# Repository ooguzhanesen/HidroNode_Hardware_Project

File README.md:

# STM32WL HidroNode – Donanım Tasarım Dokümantasyonu

> **Hazırlayan:** Oğuzhan ESEN  
> **Proje Adı:** HidroNode Board 
> **Tarih:** 24 Eylül 2025  
> **Versiyon:** v1.0
---

## İçindekiler

1. [Giriş](#1-giriş)  
2. [Tasarımın Amacı ve Kapsamı](#2-tasarımın-amacı-ve-kapsamı)  
3. [Sistem Blok Diyagramı](#3-sistem-blok-diyagramı)  
4. [Tasarım Özeti](#4-tasarım-özeti)  
5. [Şematik ve PCB](#5-şematik-ve-pcb)  
6. [Test Notları](#6-test-notları)  
7. [Geliştirme ve İyileştirme Önerileri](#7-geliştirme-ve-iyileştirme-önerileri)
---

## 1. Giriş

Bu doküman, LoraSOM Kartının taşıyıcısını  olan HidroNode kartını açıklamayı amaçlamaktadır. 
Tasarım, aşağıdaki isterleri karşılamak üzere gerçekleştirilmiştir:

- LoraSOM kartı ile pin uyumu sağlanması.
- Sensörlerle Dijital haberleşme yapabilmesi için **(TPEC)** RS485 engtegresinin bulunması.
- Sensörlerle Analog haberleşme yapabilmesi için **(Radar)** 4-20mA okuma girişinin bulunması.
- Dijital çıkış ile çalışan sensörlerden veri okuyabilmesi için **(Yağmur Sensörü)** dijital girişin bulunması.
- Arazi koşullarında Akü ve benzeri bataryalarla çalışabilmesi için 7-28 V girişi regüle edebilesi.
- Sensör çıkışlarının votajının sabitlenmesi(15v).
- Tassaruf amacıyla sensorleri kullanılmadığında kapatması.
- Dijital giriş çıkışların izole edilmesi.

---

## 2. Tasarımın Amacı ve Kapsamı
Proje kapsamında, LoraSOM kartının güvenli şekilde sensörlerden gelen verileri okuması ve çevresel şartlarda çalışması amaçlanmaktadır.

Taşıyıcı kart, aşağıdaki teknik özellikleri ile ölçüm istasyonlarındaki ihtiyaçları karşılamaktadır:

- **RS485 Haberleşme**  
  MAX3075EESA entegresi ile TPEC gibi endüstriyel sensörler ile haberleşme sağlanır.

- **Analog Sensör Girişi (4–20 mA)**  
  150 Ω shunt direnç, 2 adet opamp ve zener koruma ile akım döngülü sensörlerden gelen analog değer 16 bit çözünürlüğe sahip ADS1115IDGS entegresine bağlanır. Bu entegre de I2C ile LoraSOM'a Bağlıdır.

- **Panel Gerilim Okuma**  
  150 kΩ ve 20 kΩ direnç bölücü ile güneş panelinden voltaj ölçümü yapılabilir.

- **İzole Dijital Giriş**  
  Optokuplör korumalı 2 adet dijital giriş ile dijital çıkışlı ( yağmur sensörü) sensörlerden veri okunabilir.

- **İzole Dijital Çıkışlar**  
  4 adet dijital çıkış LTV-847S entegresi sayesinde izole şekilde röle veya kontrol elemanları sürülebilir.

- **Geniş Giriş Gerilim Aralığı**  
  TPS54302 ve TPS62291DRVR entegreleri ile 7–28 V DC giriş, 5 V ve 3.3 V seviyelerine güvenli şekilde regüle edilir.

- **Sensör Güç çıkışlarının Sabitlenmesi ve Kontrolü (15V)**  
  MT3608 entegresi ile 5v 15v yükselterek sensörlerin akü voltajına bağımlı kalması engellenmiştir. Ayrıca MT3608 entegresin enable pini ile bu çıkışlar anahtarlanmaktadır. 

---

## 3. Sistem Blok Diyagramı

## 4. Tasarım Özeti

Tasarım 4 katlı olacak şekikde KiCAD üzerinden tasarlanmıştır.

## 5. Şematik ve PCB
[Şematik için tıklayın](docs/HidroNode_Project.pdf)

.jpeg)

---
## 6. Test Notları
* 5v regülatör devresinde 75pf olmadıgı için en yakın deger olan 68pf kullanıldı.

---
## 7. Geliştirme ve İyileştirme Önerileri

* indüktör footprinti güncellenebilir.
* tvs diyot kıfı küçültülebilir.
* Genişleme portunun slikscreeni düzeltilecek. 
* Kart soket tipi degistirilebilir 

--- 

## Eksikler
* Anten kablosu alınacak.
* kart montajı için vida alınacak
* genişleme portu karsılık soketi alınacak
* hoparlor modulunun voltajı 3.3 volta dusurulecek.
* sbrr alınması gerek. 1 adet kaldı.  
* 150 ohm sont bitti.

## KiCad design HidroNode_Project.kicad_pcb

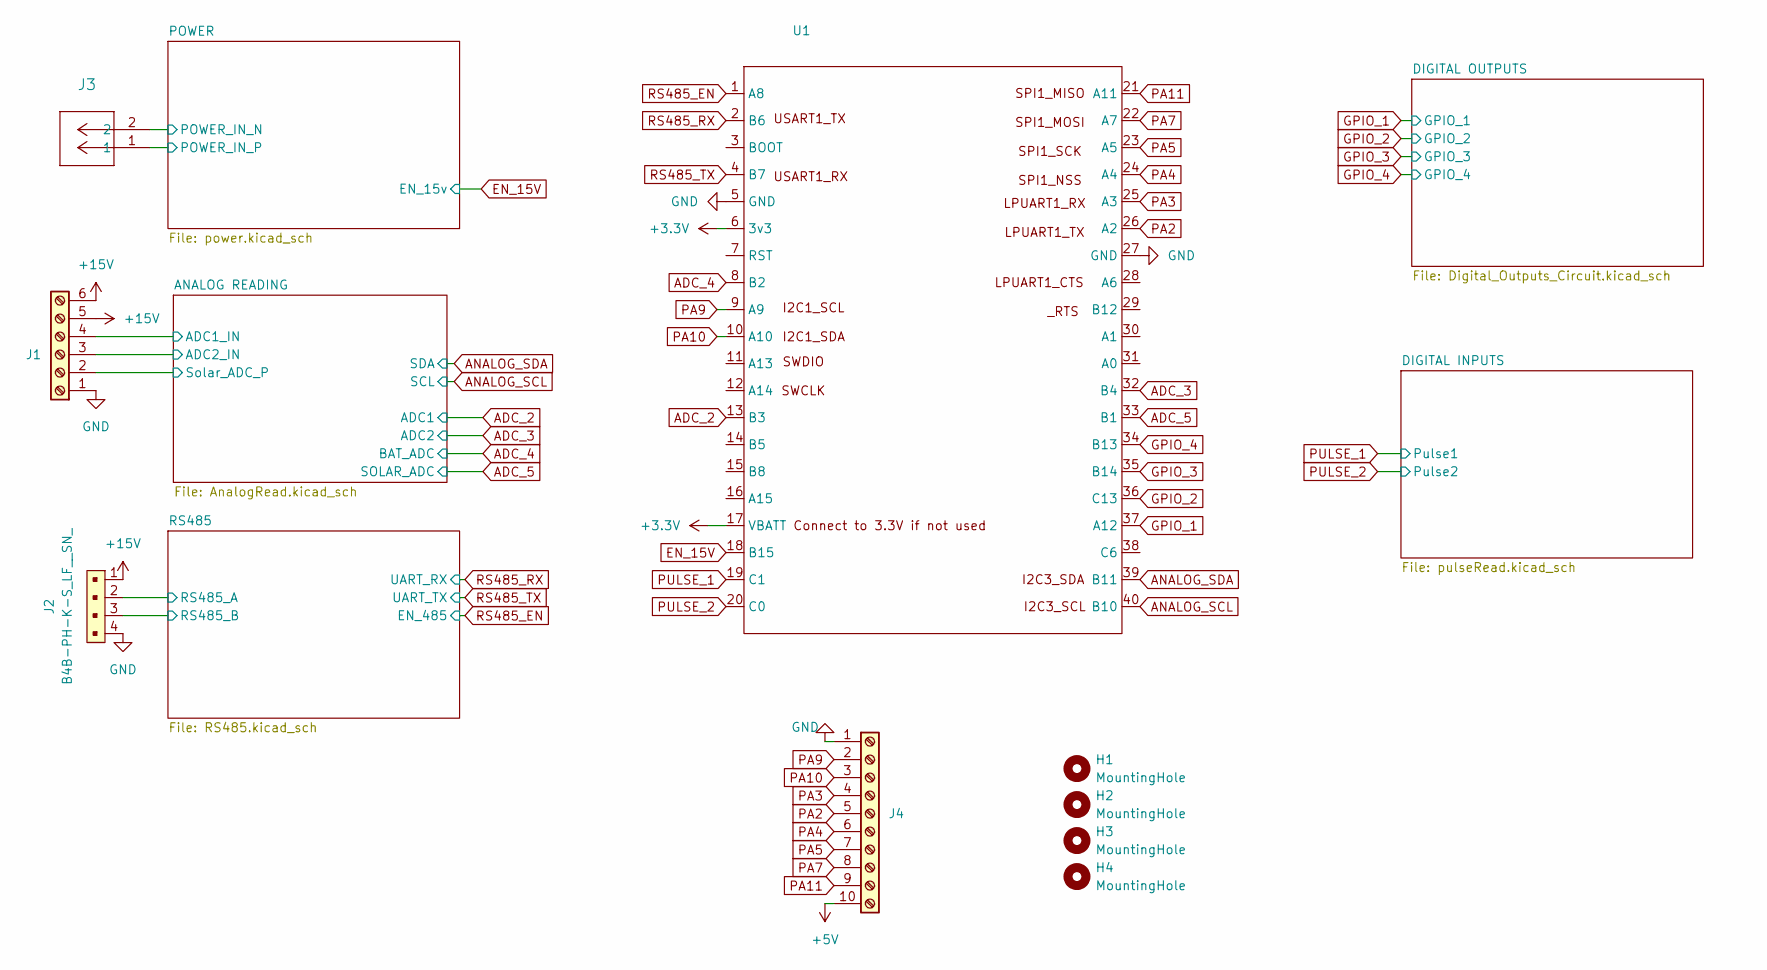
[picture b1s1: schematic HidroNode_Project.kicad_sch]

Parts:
H1, H2: MountingHole; MountingHole_3.2mm_M3_ISO14580_Pad
H3, H4: MountingHole; MountingHole_2.7mm_M2.5_DIN965_Pad
J1: Hirose_DF13-06P-1.25DSA_1x06_P1.25mm_Vertical
J2: B4B-PH-K-S_LF__SN_; Hirose_DF13-04P-1.25DSA_1x04_P1.25mm_Vertical; MPN B4B-PH-K-S(LF)(SN); Digi-Key_PN 455-1706-ND
J3: PinHeader_2x01_P2.54mm_Vertical
J4: BoxHeader2x5_1.27
U1: stm32wl_lora_som

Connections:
+3.3V: U1.6 (3v3), U1.17 (VBATT); also elsewhere on the board
+5V: J4.10; also elsewhere on the board
+15V: J1.5, J1.6, J2.1; also elsewhere on the board
/ANALOG READING/ADC1_IN: J1.4; also elsewhere on the board
/ANALOG READING/ADC2_IN: J1.3; also elsewhere on the board
/ANALOG READING/Solar_ADC_P: J1.2; also elsewhere on the board
/POWER/POWER_IN_N: J3.2; also elsewhere on the board
/POWER/POWER_IN_P: J3.1; also elsewhere on the board
/RS485/RS485_A: J2.2; also elsewhere on the board
/RS485/RS485_B: J2.3; also elsewhere on the board
ADC_2: U1.13 (B3); also elsewhere on the board
ADC_3: U1.32 (B4); also elsewhere on the board
ADC_4: U1.8 (B2); also elsewhere on the board
ADC_5: U1.33 (B1); also elsewhere on the board
ANALOG_SCL: U1.40 (B10); also elsewhere on the board
ANALOG_SDA: U1.39 (B11); also elsewhere on the board
EN_15V: U1.18 (B15); also elsewhere on the board
GND: J1.1, J2.4, J4.1, U1.5 (GND), U1.27 (GND); also elsewhere on the board
GPIO_1: U1.37 (A12); also elsewhere on the board
GPIO_2: U1.36 (C13); also elsewhere on the board
GPIO_3: U1.35 (B14); also elsewhere on the board
GPIO_4: U1.34 (B13); also elsewhere on the board
PA2: J4.5, U1.26 (A2)
PA3: J4.4, U1.25 (A3)
PA4: J4.6, U1.24 (A4)
PA5: J4.7, U1.23 (A5)
PA7: J4.8, U1.22 (A7)
PA9: J4.2, U1.9 (A9)
PA10: J4.3, U1.10 (A10)
PA11: J4.9, U1.21 (A11)
PULSE_1: U1.19 (C1); also elsewhere on the board
PULSE_2: U1.20 (C0); also elsewhere on the board
RS485_EN: U1.1 (A8); also elsewhere on the board
RS485_RX: U1.2 (B6); also elsewhere on the board
RS485_TX: U1.4 (B7); also elsewhere on the board

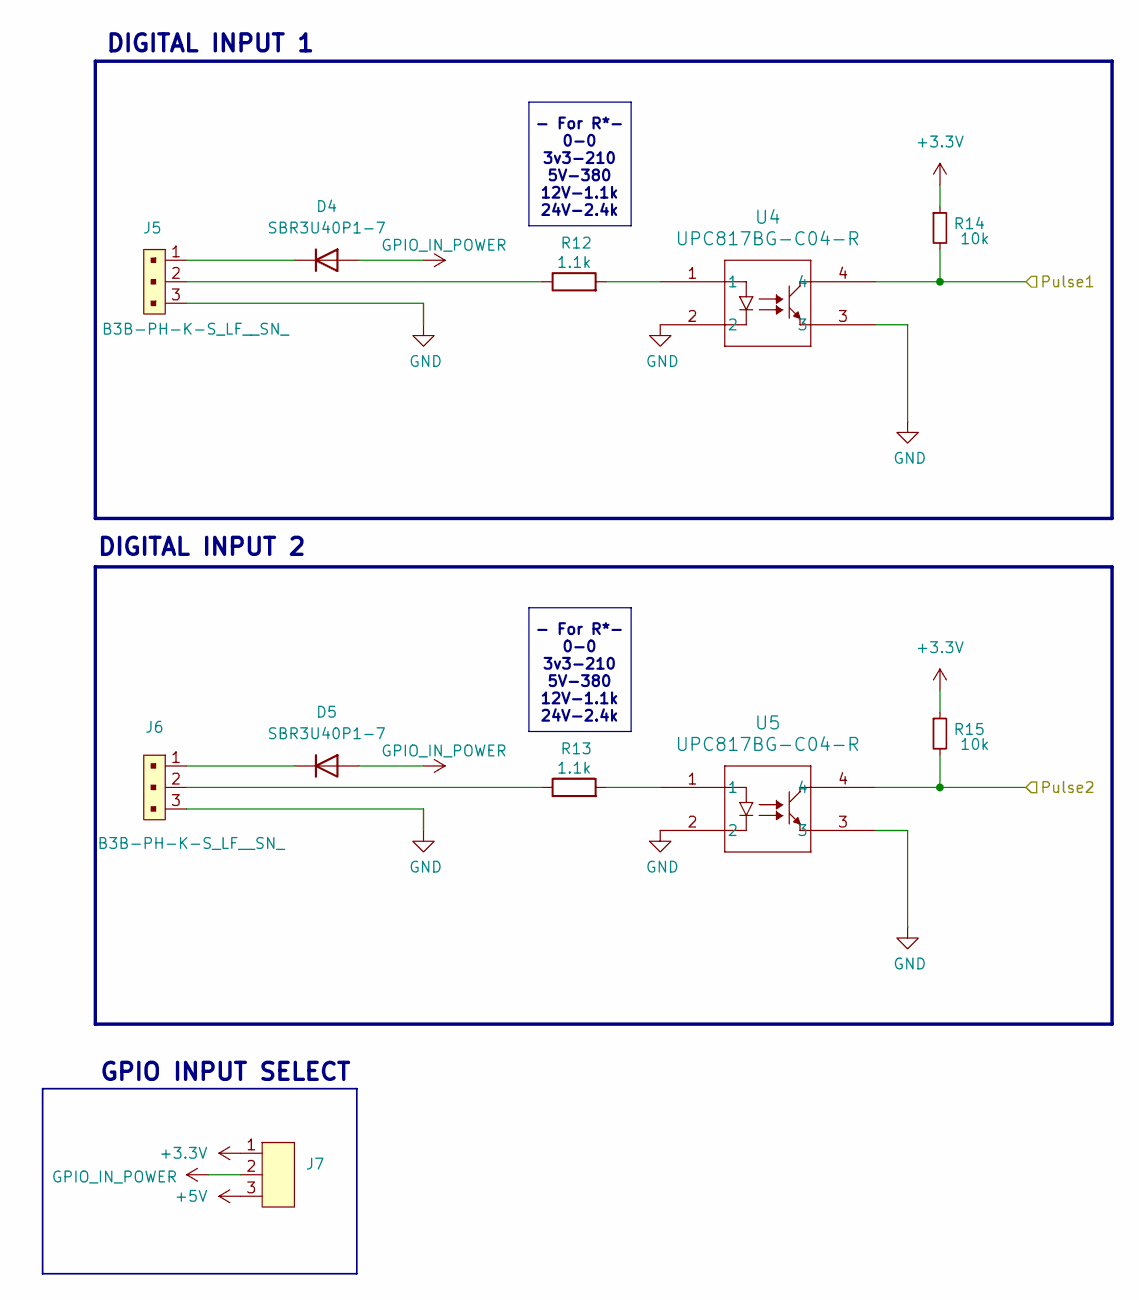
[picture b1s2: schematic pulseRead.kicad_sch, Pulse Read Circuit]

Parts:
D4, D5: SBR3U40P1-7; D_PowerDI-123
J5, J6: B3B-PH-K-S_LF__SN_; Molex_PicoBlade_53047-0310_1x03_P1.25mm_Vertical; MPN B3B-PH-K-S(LF)(SN); DigiKey 277-1207-ND
J7: PinHeader_1x03_P2.54mm_Vertical
R12, R13: 1.1k; R_0603_1608Metric_Pad0.98x0.95mm_HandSolder
R14, R15: 10k; R_0603_1608Metric_Pad0.98x0.95mm_HandSolder
U4, U5: UPC817BG-C04-R; EL8171-S1-TU_EVE; DigiKey 080-1603-2-ND

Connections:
+3.3V: J7.1, R14.1, R15.1; also elsewhere on the board
+5V: J7.3; also elsewhere on the board
GND: J5.3, J6.3, U4.2, U4.3, U5.2, U5.3; also elsewhere on the board
GPIO_IN_POWER: D4.2 (A), D5.2 (A), J7.2
unnamed: D4.1 (K), J5.1
unnamed: D5.1 (K), J6.1
unnamed: J5.2, R12.1
unnamed: J6.2, R13.1
unnamed: R12.2, U4.1
unnamed: R13.2, U5.1
PULSE_1: R14.2, U4.4; also elsewhere on the board
PULSE_2: R15.2, U5.4; also elsewhere on the board

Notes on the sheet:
GPIO INPUT SELECT
DIGITAL INPUT 1
DIGITAL INPUT 2
- For R*- 0-0 3v3-210 5V-380 12V-1.1k 24V-2.4k

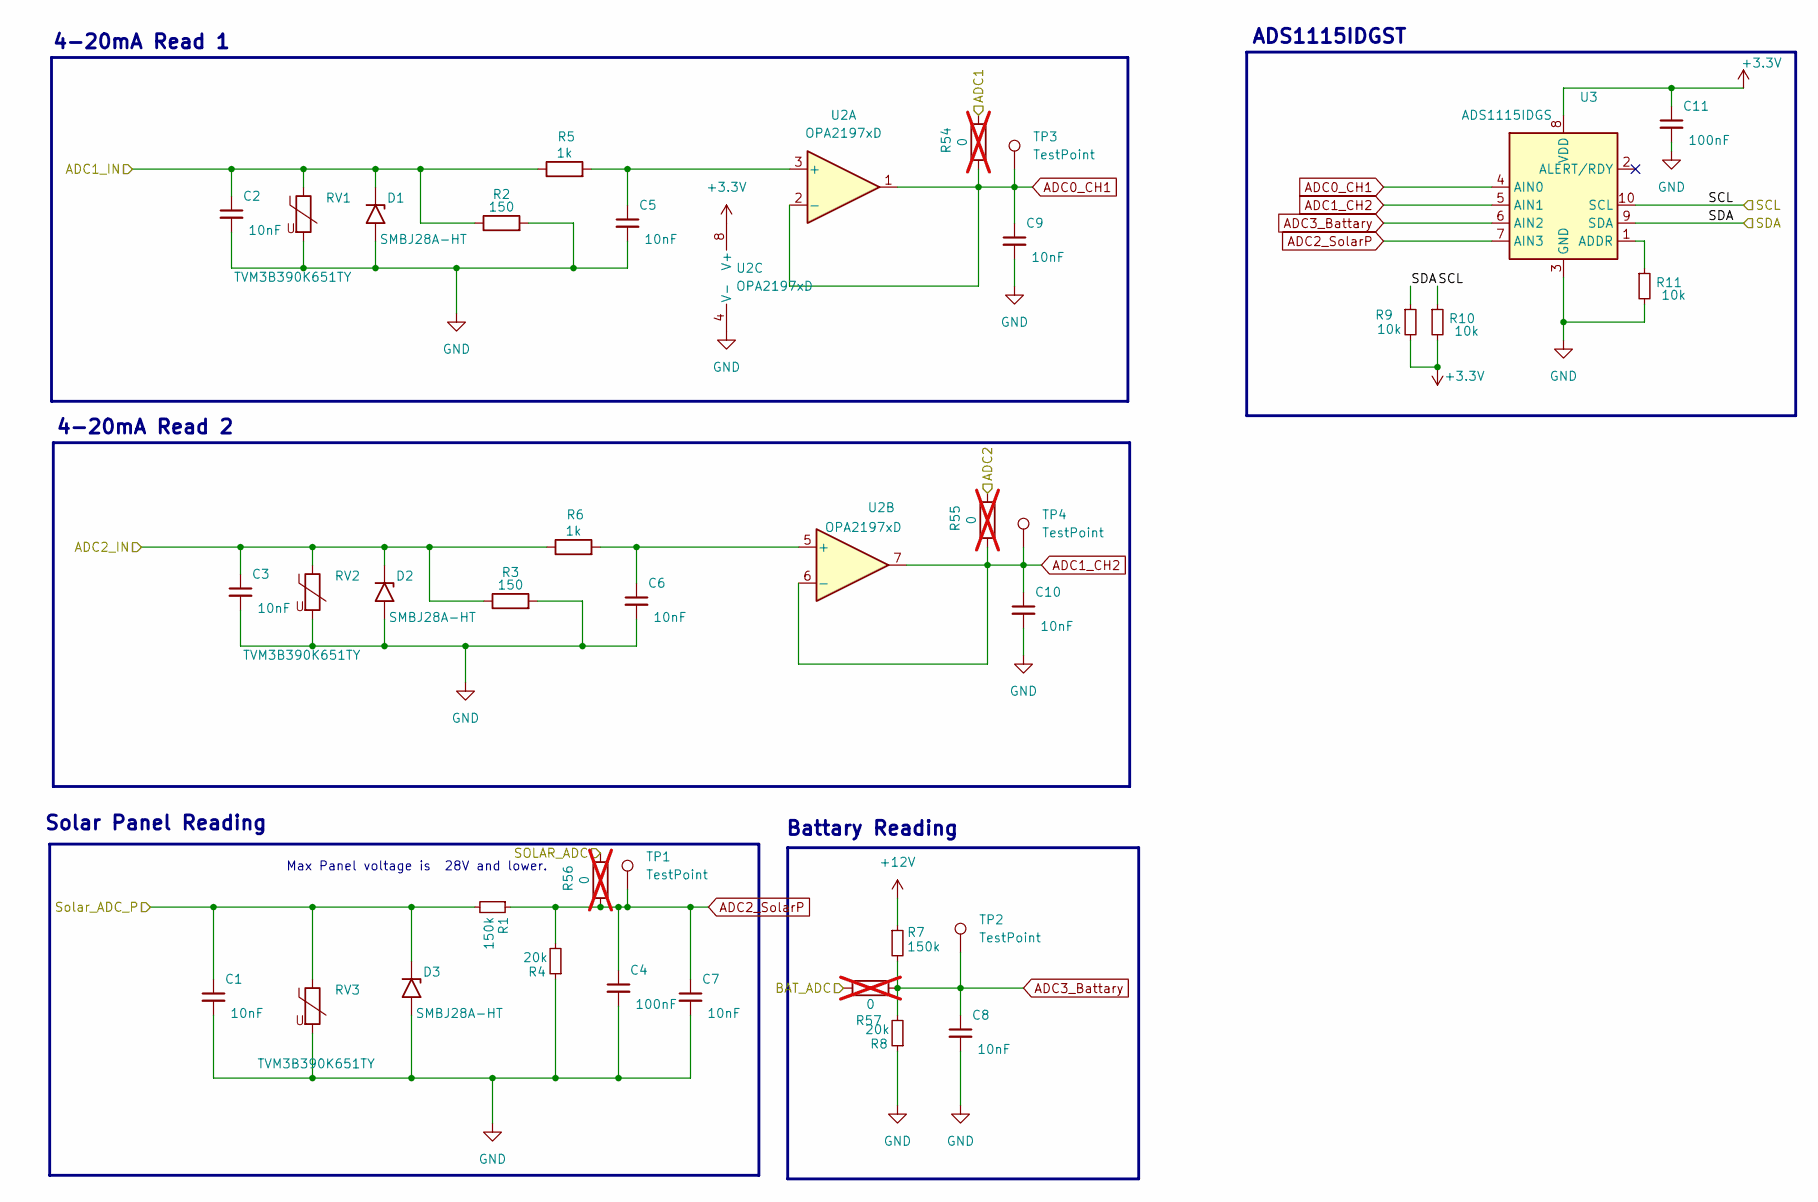
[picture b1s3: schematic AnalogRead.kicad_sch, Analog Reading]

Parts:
C1, C2, C3, C5, C6, C7, C8, C9, C10: 10nF; C_0603_1608Metric_Pad1.08x0.95mm_HandSolder
C4, C11: 100nF; C_0603_1608Metric_Pad1.08x0.95mm_HandSolder
D1, D2, D3: SMBJ28A-HT; D_SMB_Handsoldering
R1, R7: 150k; R_0805_2012Metric_Pad1.20x1.40mm_HandSolder
R2, R3: 150; R_1210_3225Metric
R4, R8: 20k; R_0805_2012Metric_Pad1.20x1.40mm_HandSolder
R5, R6: 1k; R_0603_1608Metric_Pad0.98x0.95mm_HandSolder
R9, R10, R11: 10k; R_0603_1608Metric_Pad0.98x0.95mm_HandSolder
R54, R55, R56, R57: 0; R_0603_1608Metric_Pad0.98x0.95mm_HandSolder; not fitted
RV1, RV2, RV3: TVM3B390K651TY; R_1206_3216Metric_Pad1.30x1.75mm_HandSolder
TP1, TP2, TP3, TP4: TestPoint; TestPoint_Loop_D2.60mm_Drill0.9mm_Beaded
U2: OPA2197xD; SOIC-8_3.9x4.9mm_P1.27mm
U3: ADS1115IDGS; TSSOP-10_3x3mm_P0.5mm

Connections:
+3.3V: C11.1, R9.2, R10.2, U2.8 (V+), U3.8 (VDD); also elsewhere on the board
+12V: R7.1; also elsewhere on the board
/ANALOG READING/ADC1_IN: C2.1, D1.1 (A1), R2.1, R5.1, RV1.1; also elsewhere on the board
/ANALOG READING/ADC2_IN: C3.1, D2.1 (A1), R3.1, R6.1, RV2.1; also elsewhere on the board
/ANALOG READING/Solar_ADC_P: C1.1, D3.1 (A1), R1.2, RV3.1; also elsewhere on the board
ADC0_CH1: C9.1, R54.1, TP3.1, U2.1, U2.2 (-), U3.4 (AIN0)
ADC1_CH2: C10.1, R55.1, TP4.1, U2.6 (-), U2.7, U3.5 (AIN1)
ADC2_SolarP: C4.1, C7.1, R1.1, R4.2, R56.1, TP1.1, U3.7 (AIN3)
ADC3_Battary: C8.1, R7.2, R8.2, R57.1, TP2.1, U3.6 (AIN2)
ADC_2: R54.2; also elsewhere on the board
ADC_3: R55.2; also elsewhere on the board
ADC_4: R57.2; also elsewhere on the board
ADC_5: R56.2; also elsewhere on the board
ANALOG_SCL: R10.1, U3.10 (SCL); also elsewhere on the board
ANALOG_SDA: R9.1, U3.9 (SDA); also elsewhere on the board
GND: C1.2, C2.2, C3.2, C4.2, C5.2, C6.2, C7.2, C8.2, C9.2, C10.2, C11.2, D1.2 (A2), D2.2 (A2), D3.2 (A2), R2.2, R3.2, R4.1, R8.1, R11.2, RV1.2, RV2.2, RV3.2, U2.4 (V-), U3.3 (GND); also elsewhere on the board
unnamed: C5.1, R5.2, U2.3 (+)
unnamed: C6.1, R6.2, U2.5 (+)
unnamed: R11.1, U3.1 (ADDR)

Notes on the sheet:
Battary Reading
4-20mA Read 2
Solar Panel Reading
4-20mA Read 1
ADS1115IDGST
Max Panel voltage is 28V and lower.

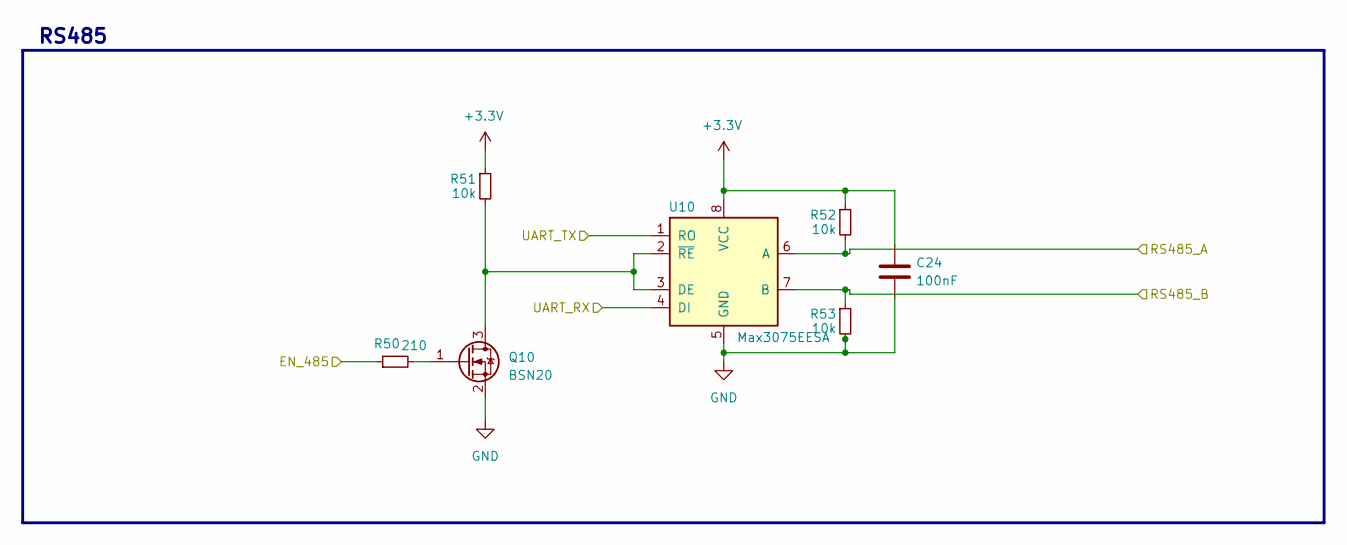
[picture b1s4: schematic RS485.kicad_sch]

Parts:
C24: 100nF; C_0603_1608Metric_Pad1.08x0.95mm_HandSolder; DIGIKEY 3372-0402B104K500HITR-ND
Q10: BSN20; SOT-23; DIGIKEY BSN20-7DITR-ND
R50: 210; R_0603_1608Metric_Pad0.98x0.95mm_HandSolder; DIGIKEY 541-0.0GTR-ND
R51, R52, R53: 10k; R_0603_1608Metric_Pad0.98x0.95mm_HandSolder
U10: Max3075EESA; SOIC-8_3.9x4.9mm_P1.27mm; DIGIKEY MAX3075EESA+-ND

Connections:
+3.3V: C24.1, R51.1, R52.1, U10.8 (VCC); also elsewhere on the board
/RS485/RS485_A: R52.2, U10.6 (A); also elsewhere on the board
/RS485/RS485_B: R53.1, U10.7 (B); also elsewhere on the board
GND: C24.2, Q10.2 (S), R53.2, U10.5 (GND); also elsewhere on the board
unnamed: Q10.3 (D), R51.2, U10.2 (~RE), U10.3 (DE)
unnamed: Q10.1 (G), R50.2
RS485_EN: R50.1; also elsewhere on the board
RS485_RX: U10.4 (DI); also elsewhere on the board
RS485_TX: U10.1 (RO); also elsewhere on the board

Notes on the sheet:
RS485

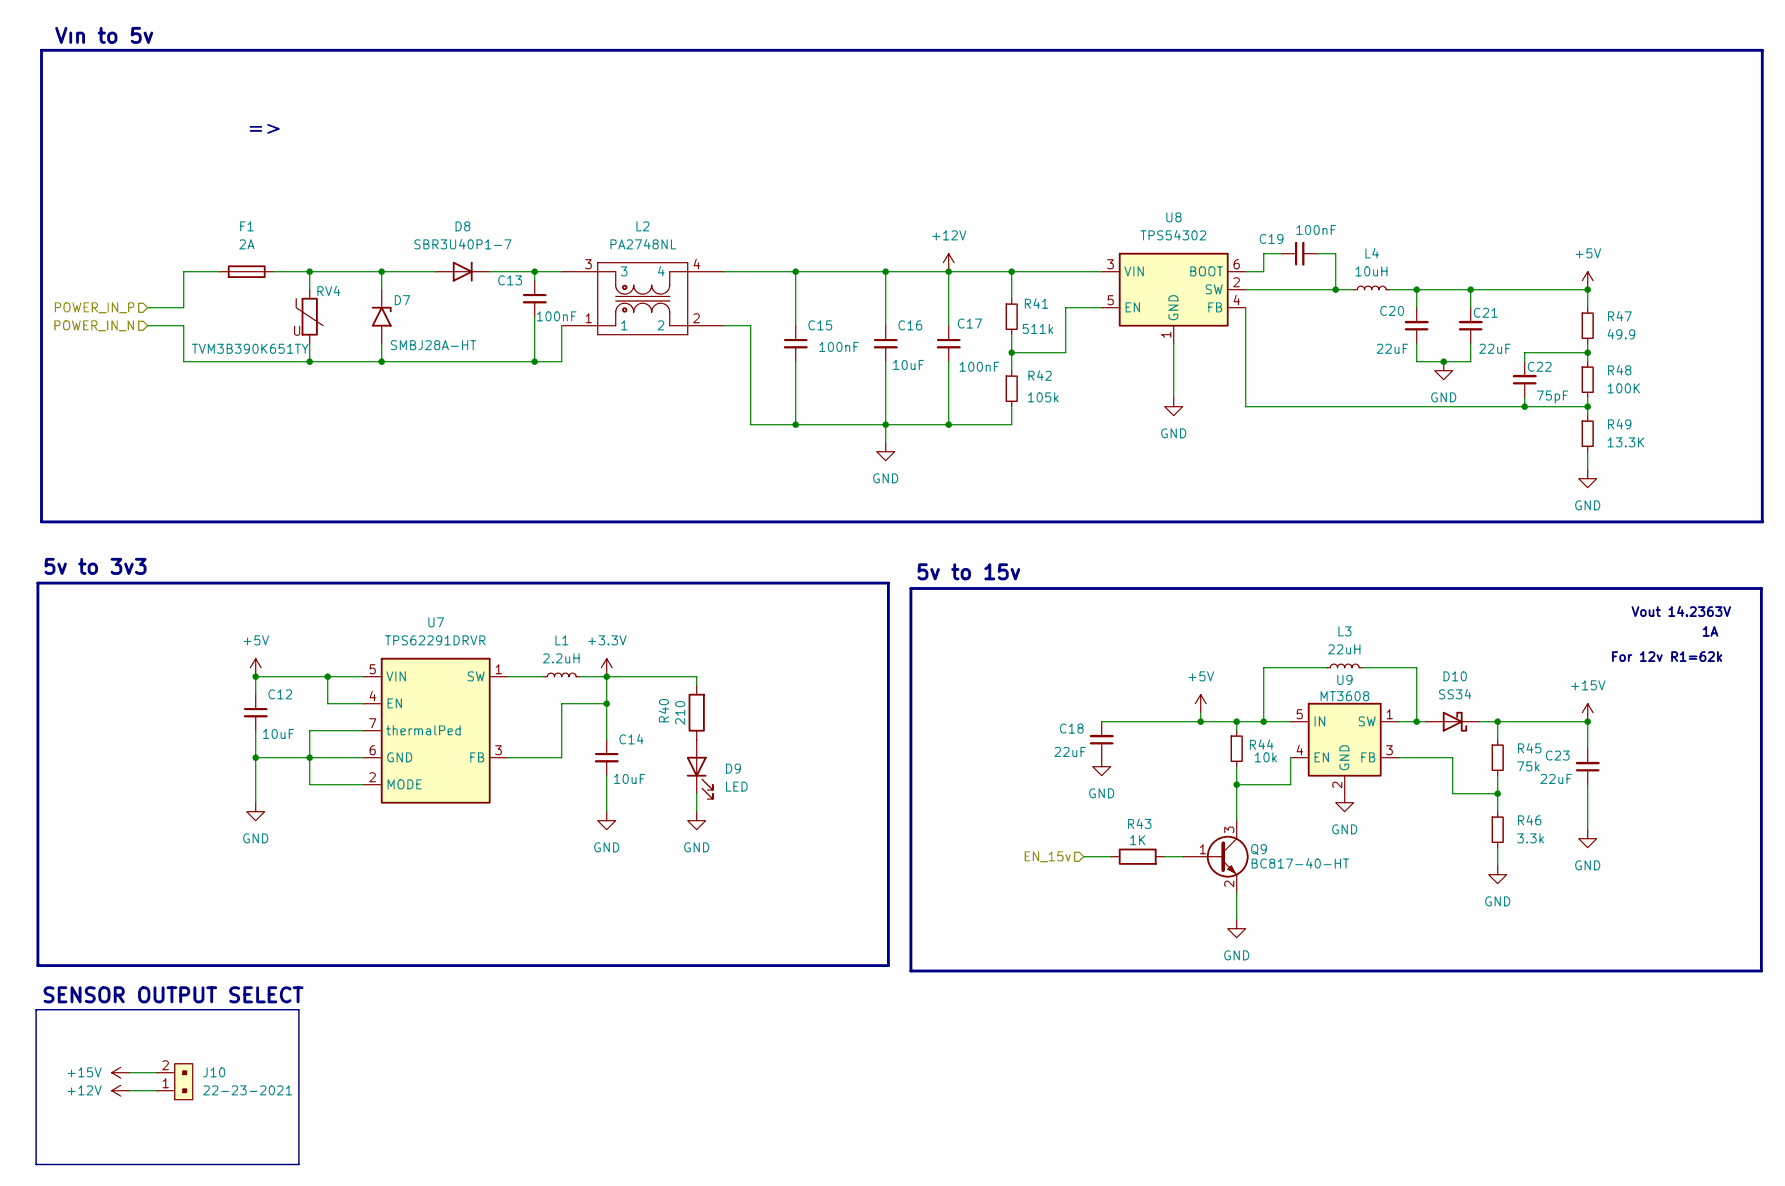
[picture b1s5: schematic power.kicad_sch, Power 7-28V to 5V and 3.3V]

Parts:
C12: 10uF; C_0603_1608Metric
C13, C15, C17, C19: 100nF; C_0603_1608Metric_Pad1.08x0.95mm_HandSolder
C14: 10uF; C_0603_1608Metric_Pad1.08x0.95mm_HandSolder
C16: 10uF; LED_0805_2012Metric_Pad1.15x1.40mm_HandSolder
C18, C23: 22uF; C_1206_3216Metric_Pad1.33x1.80mm_HandSolder
C20, C21: 22uF; C_0603_1608Metric_Pad1.08x0.95mm_HandSolder
C22: 75pF; C_0603_1608Metric_Pad1.08x0.95mm_HandSolder
D7: SMBJ28A-HT; D_SMB_Handsoldering
D8: SBR3U40P1-7; D_PowerDI-123
D9: LED; LED_0603_1608Metric_Pad1.05x0.95mm_HandSolder
D10: SS34; DO-214AB
F1: 2A; Fuse_0603_1608Metric_Pad1.05x0.95mm_HandSolder
J10: 22-23-2021; PinHeader_1x2_P2.54mm_Drill1.02mm; MPN 22-23-2021; Digi-Key_PN WM4200-ND
L1: 2.2uH; L_Murata_DFE201610P
L2: PA2748NL; pa2748
L3: 22uH; L_12x12mm_H6mm
L4: 10uH; INDC6060X300
Q9: BC817-40-HT; SOT-23
R40: 210; R_0603_1608Metric_Pad0.98x0.95mm_HandSolder
R41: 511k; R_0603_1608Metric_Pad0.98x0.95mm_HandSolder
R42: 105k; R_0603_1608Metric_Pad0.98x0.95mm_HandSolder
R43: 1K; R_0603_1608Metric_Pad0.98x0.95mm_HandSolder; DigiKey 311-210HRTR-ND
R44: 10k; R_0603_1608Metric_Pad0.98x0.95mm_HandSolder
R45: 75k; R_0603_1608Metric_Pad0.98x0.95mm_HandSolder
R46: 3.3k; R_0603_1608Metric_Pad0.98x0.95mm_HandSolder
R47: 49.9; R_0603_1608Metric_Pad0.98x0.95mm_HandSolder
R48: 100K; R_0603_1608Metric_Pad0.98x0.95mm_HandSolder
R49: 13.3K; R_0603_1608Metric_Pad0.98x0.95mm_HandSolder; DIGIKEY 0603SAF1332T5E
RV4: TVM3B390K651TY; R_1206_3216Metric_Pad1.30x1.75mm_HandSolder
U7: TPS62291DRVR; WSON6 (2x2)
U8: TPS54302; SOT-23-6
U9: MT3608; SOT-23-6

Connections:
+3.3V: C14.1, L1.2, R40.2, U7.3 (FB); also elsewhere on the board
+5V: C12.1, C18.2, C20.2, C21.2, L3.1, L4.2, R44.1, R47.1, U7.4 (EN), U7.5 (VIN), U9.5 (IN); also elsewhere on the board
+12V: C15.1, C16.1, C17.1, J10.1, L2.4, R41.1, U8.3 (VIN); also elsewhere on the board
+15V: C23.2, D10.K, J10.2, R45.1; also elsewhere on the board
/POWER/POWER_IN_N: C13.2, D7.2 (A2), L2.1, RV4.2; also elsewhere on the board
/POWER/POWER_IN_P: F1.2; also elsewhere on the board
EN_15V: R43.1; also elsewhere on the board
GND: C12.2, C14.2, C15.2, C16.2, C17.2, C18.1, C20.1, C21.1, C23.1, D9.1 (K), L2.2, Q9.2 (E), R42.2, R46.2, R49.2, U7.2 (MODE), U7.6 (GND), U7.7 (thermalPed), U8.1 (GND), U9.2 (GND); also elsewhere on the board
unnamed: C22.2, R47.2, R48.1
unnamed: D7.1 (A1), D8.2 (A), F1.1, RV4.1
unnamed: C13.1, D8.1 (K), L2.3
unnamed: D9.2 (A), R40.1
unnamed: Q9.1 (B), R43.2
unnamed: Q9.3 (C), R44.2, U9.4 (EN)
unnamed: L1.1, U7.1 (SW)
unnamed: C19.1, U8.6 (BOOT)
unnamed: R41.2, R42.1, U8.5 (EN)
unnamed: C22.1, R48.2, R49.1, U8.4 (FB)
unnamed: C19.2, L4.1, U8.2 (SW)
unnamed: R45.2, R46.1, U9.3 (FB)
unnamed: D10.A, L3.2, U9.1 (SW)

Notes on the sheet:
Vın to 5v
For 12v R1=62k
5v to 3v3
5v to 15v
Vout 14.2363V
SENSOR OUTPUT SELECT

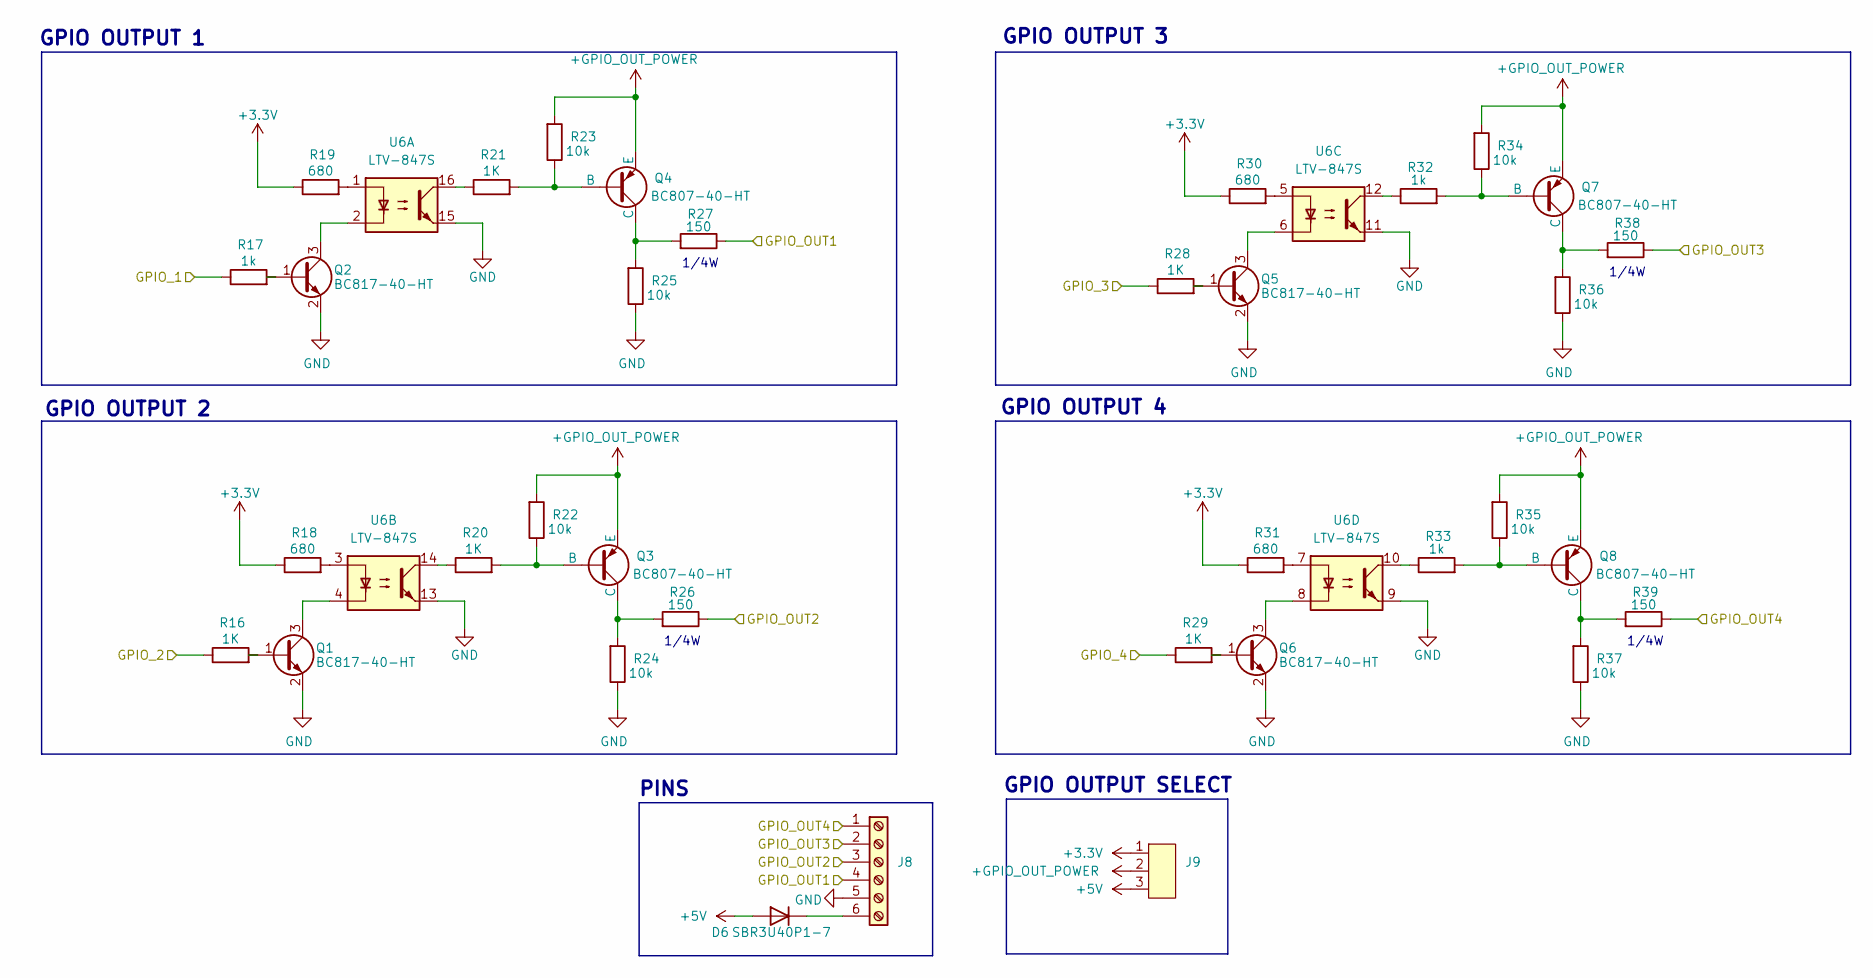
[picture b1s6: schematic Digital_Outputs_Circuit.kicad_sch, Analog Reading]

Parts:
D6: SBR3U40P1-7; D_PowerDI-123
J8: Hirose_DF13-06P-1.25DSA_1x06_P1.25mm_Vertical
J9: PinHeader_1x03_P2.54mm_Vertical
Q1, Q2, Q5, Q6: BC817-40-HT; SOT-23
Q3, Q4, Q7, Q8: BC807-40-HT; SOT-23-3
R16, R20, R21: 1K; R_0603_1608Metric_Pad0.98x0.95mm_HandSolder; DigiKey CRT03F7E1001
R17: 1k; R_0603_1608Metric_Pad0.98x0.95mm_HandSolder
R18, R19, R30, R31: 680; R_0603_1608Metric_Pad0.98x0.95mm_HandSolder; DigiKey 311-210HRTR-ND
R22, R23, R24, R25, R34, R35, R36, R37: 10k; R_0603_1608Metric_Pad0.98x0.95mm_HandSolder; DigiKey 311-210HRTR-ND
R26, R27, R38, R39: 150; R_1206_3216Metric_Pad1.30x1.75mm_HandSolder; DigiKey 311-210HRTR-ND
R28, R29: 1K; R_0603_1608Metric_Pad0.98x0.95mm_HandSolder; DigiKey 311-210HRTR-ND
R32, R33: 1k; R_0603_1608Metric_Pad0.98x0.95mm_HandSolder; DigiKey 311-210HRTR-ND
U6: LTV-847S; SMDIP-16_W9.53mm

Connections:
+3.3V: J9.1, R18.1, R19.1, R30.1, R31.1; also elsewhere on the board
+5V: D6.2 (A), J9.3; also elsewhere on the board
+GPIO_OUT_POWER: J9.2, Q3.2 (E), Q4.2 (E), Q7.2 (E), Q8.2 (E), R22.2, R23.2, R34.2, R35.2
/DIGITAL OUTPUTS/GPIO_OUT1: J8.4, R27.1
/DIGITAL OUTPUTS/GPIO_OUT2: J8.3, R26.1
/DIGITAL OUTPUTS/GPIO_OUT3: J8.2, R38.1
/DIGITAL OUTPUTS/GPIO_OUT4: J8.1, R39.1
GND: J8.5, Q1.2 (E), Q2.2 (E), Q5.2 (E), Q6.2 (E), R24.1, R25.1, R36.1, R37.1, U6.9, U6.11, U6.13, U6.15; also elsewhere on the board
GPIO_1: R17.1; also elsewhere on the board
GPIO_2: R16.1; also elsewhere on the board
GPIO_3: R28.1; also elsewhere on the board
GPIO_4: R29.1; also elsewhere on the board
unnamed: D6.1 (K), J8.6
unnamed: Q1.1 (B), R16.2
unnamed: Q1.3 (C), U6.4
unnamed: Q2.1 (B), R17.2
unnamed: Q2.3 (C), U6.2
unnamed: Q3.1 (B), R20.2, R22.1
unnamed: Q3.3 (C), R24.2, R26.2
unnamed: Q4.1 (B), R21.2, R23.1
unnamed: Q4.3 (C), R25.2, R27.2
unnamed: Q5.1 (B), R28.2
unnamed: Q5.3 (C), U6.6
unnamed: Q6.1 (B), R29.2
unnamed: Q6.3 (C), U6.8
unnamed: Q7.1 (B), R32.2, R34.1
unnamed: Q7.3 (C), R36.2, R38.2
unnamed: Q8.1 (B), R33.2, R35.1
unnamed: Q8.3 (C), R37.2, R39.2
unnamed: R18.2, U6.3
unnamed: R19.2, U6.1
unnamed: R20.1, U6.14
unnamed: R21.1, U6.16
unnamed: R30.2, U6.5
unnamed: R31.2, U6.7
unnamed: R32.1, U6.12
unnamed: R33.1, U6.10

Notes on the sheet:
GPIO OUTPUT 1
PINS
GPIO OUTPUT 2
1/4W
GPIO OUTPUT SELECT
GPIO OUTPUT 4
GPIO OUTPUT 3

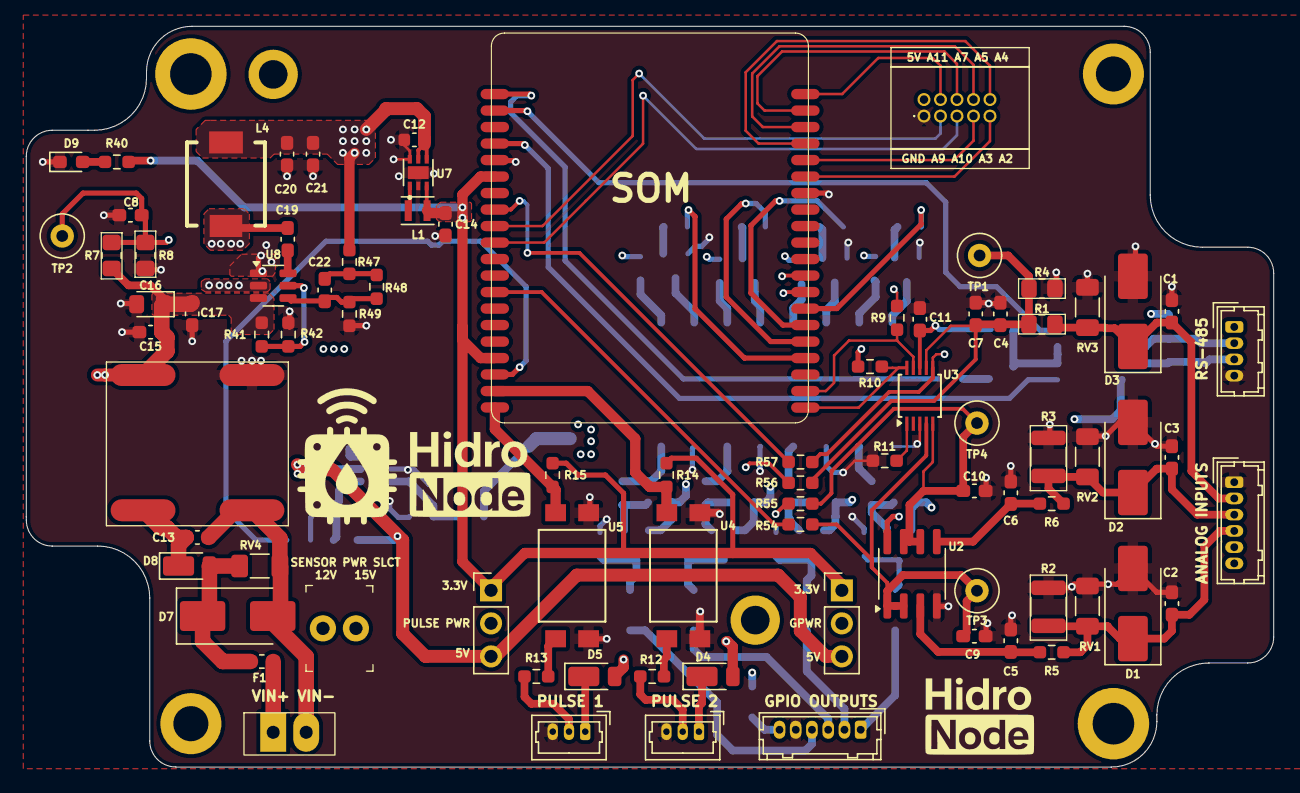
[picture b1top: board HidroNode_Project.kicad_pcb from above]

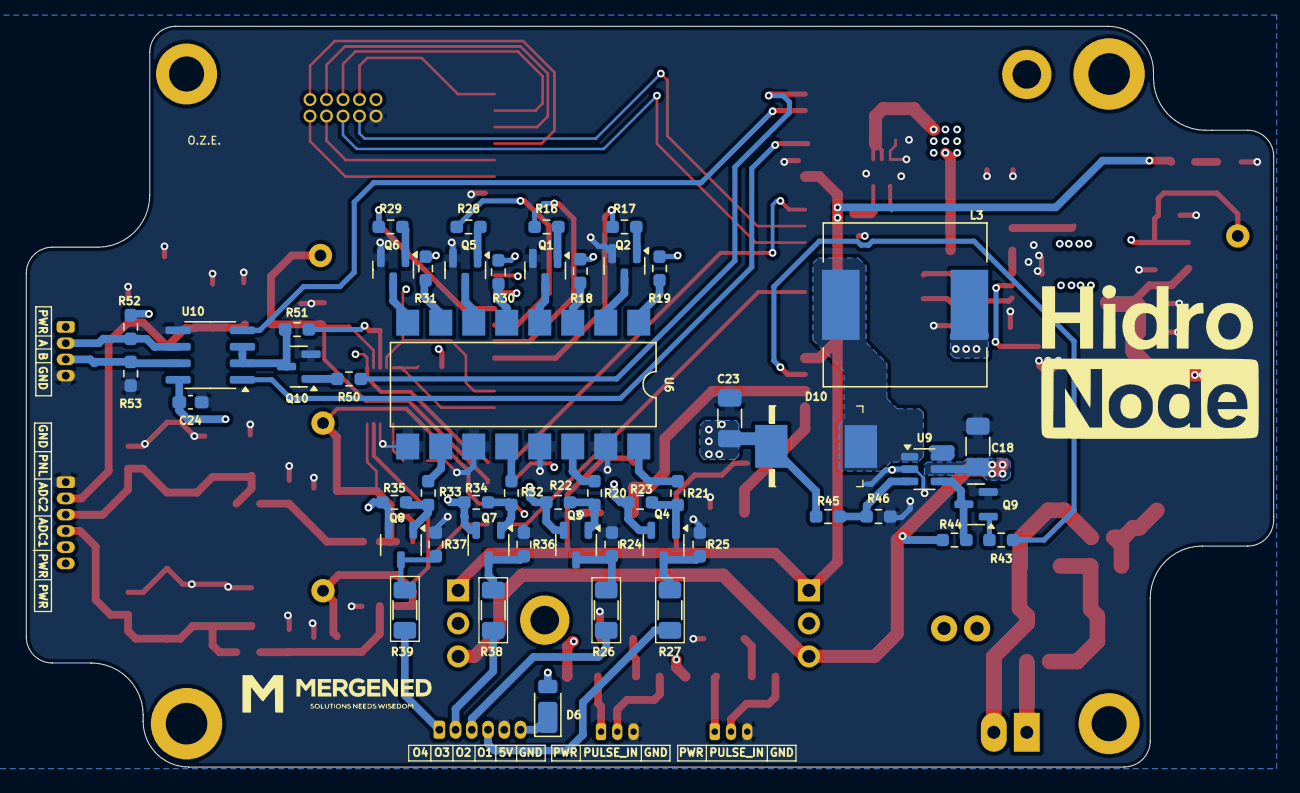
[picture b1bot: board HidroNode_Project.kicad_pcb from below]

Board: 4 copper layers, 96.0 x 57.0 mm, 138 parts (51 on the bottom side), 95 nets.

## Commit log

2025-12-24 last commit
